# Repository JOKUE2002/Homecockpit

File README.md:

# Homecockpit

## What is it?
The homecockpit is a piece of hardware, that emulates a cockpit for a given computergame.
In this case we're emulating a "universal" cockpit in M$ FSX:SE.
"Universal" means, that it is adapted, so that it can be used on any aircraft type.

## What is the main concept?
The main concept is to have a big frame with cutouts, where panels are _slotted_. 
The frame features:
* space for 7 panels (6x 20x10cm + 1x 10x20cm), 
* a cutout for a monitor to show more complex instruments (PFD, GPS, ...)
* a cutout to fit the saitek yoke
* a powerbar
* an Arduino MEGA as the "brain"

## Which panels are already finished?
* Basic LightsPanel
  * bunch of simple two-state-switches to control lights in and around the aircraft
  * hardware nearly done ( First set of switches done, needs integration with Sim-commands panel)
  * software 0%
* Basic RadioPanel
  * 2 frequency displays + 1 knob (to set s/b freqency)
  * Hardware done (100%)
  * Software still WIP (w/ main firmare)
* AutopilotPanel Part 1
  * CRS, HDG, SPD displays + knobs
  * hardware done (100%)
  * software still WIP (w/ main firmare), but a beta has already been written and tested
* AutopilotPanel Part 2
  * ALT, V/S displays + knobs
  * hardware done (100%)
  * same software as AutopilotPanel Part 1
* Advanced RadioPanel
  * SQUAWK display + setting buttons; com/nav selector/switch buttons
  * hardware work in progress (50% done)
  * software not yet started, but easy (0%)
* Landing gear lever
  * lever with pull function to lock it into three positions (UP, LK, DN)
  * hardware WIP (lever done , installation + wiring missing)
  * software 0%
  
## Which panels are still planned?
* Sim-commands panel
  * buttons to command fsx (pause, slew mode, kneeboard, ...)
* Electrical panel
  * Hydraulics, APU, Generators, ...
* Engine Panel
  * Engine starters, fire suppresion, ...

## What's included?
In the "_pcb_" folder, there are the EAGLE **.sch**ematic/**.b**oa**rd** files for the custom PCBs we designed and ordered to make things easier.
In the "_firmware_" folder there are nearly all iterations of the firmaware, including the current version ("_FSX_3.0_").
In the "_parts_" folder there is a list of all the parts, that have been used to build the cockpit.

## How much is done is it?
If we had to guess this would be like one third done. There are still ~~a few~~ a lot of the planned panels missing. Also the main frame is still a work in progress.

### Individual statuses
* Frame: 70%
* Firmware: 40%
* Panels: 40%
* whole project: 30%

## Who's contributing?
Currently there are two main contributers:
Jonas (Hardware & Software specialist)
Cornelius (Flightsim/flying & design specialist)

## How can you contact us / help us?
Just create an issue. We'll answer on it as soon as possible.

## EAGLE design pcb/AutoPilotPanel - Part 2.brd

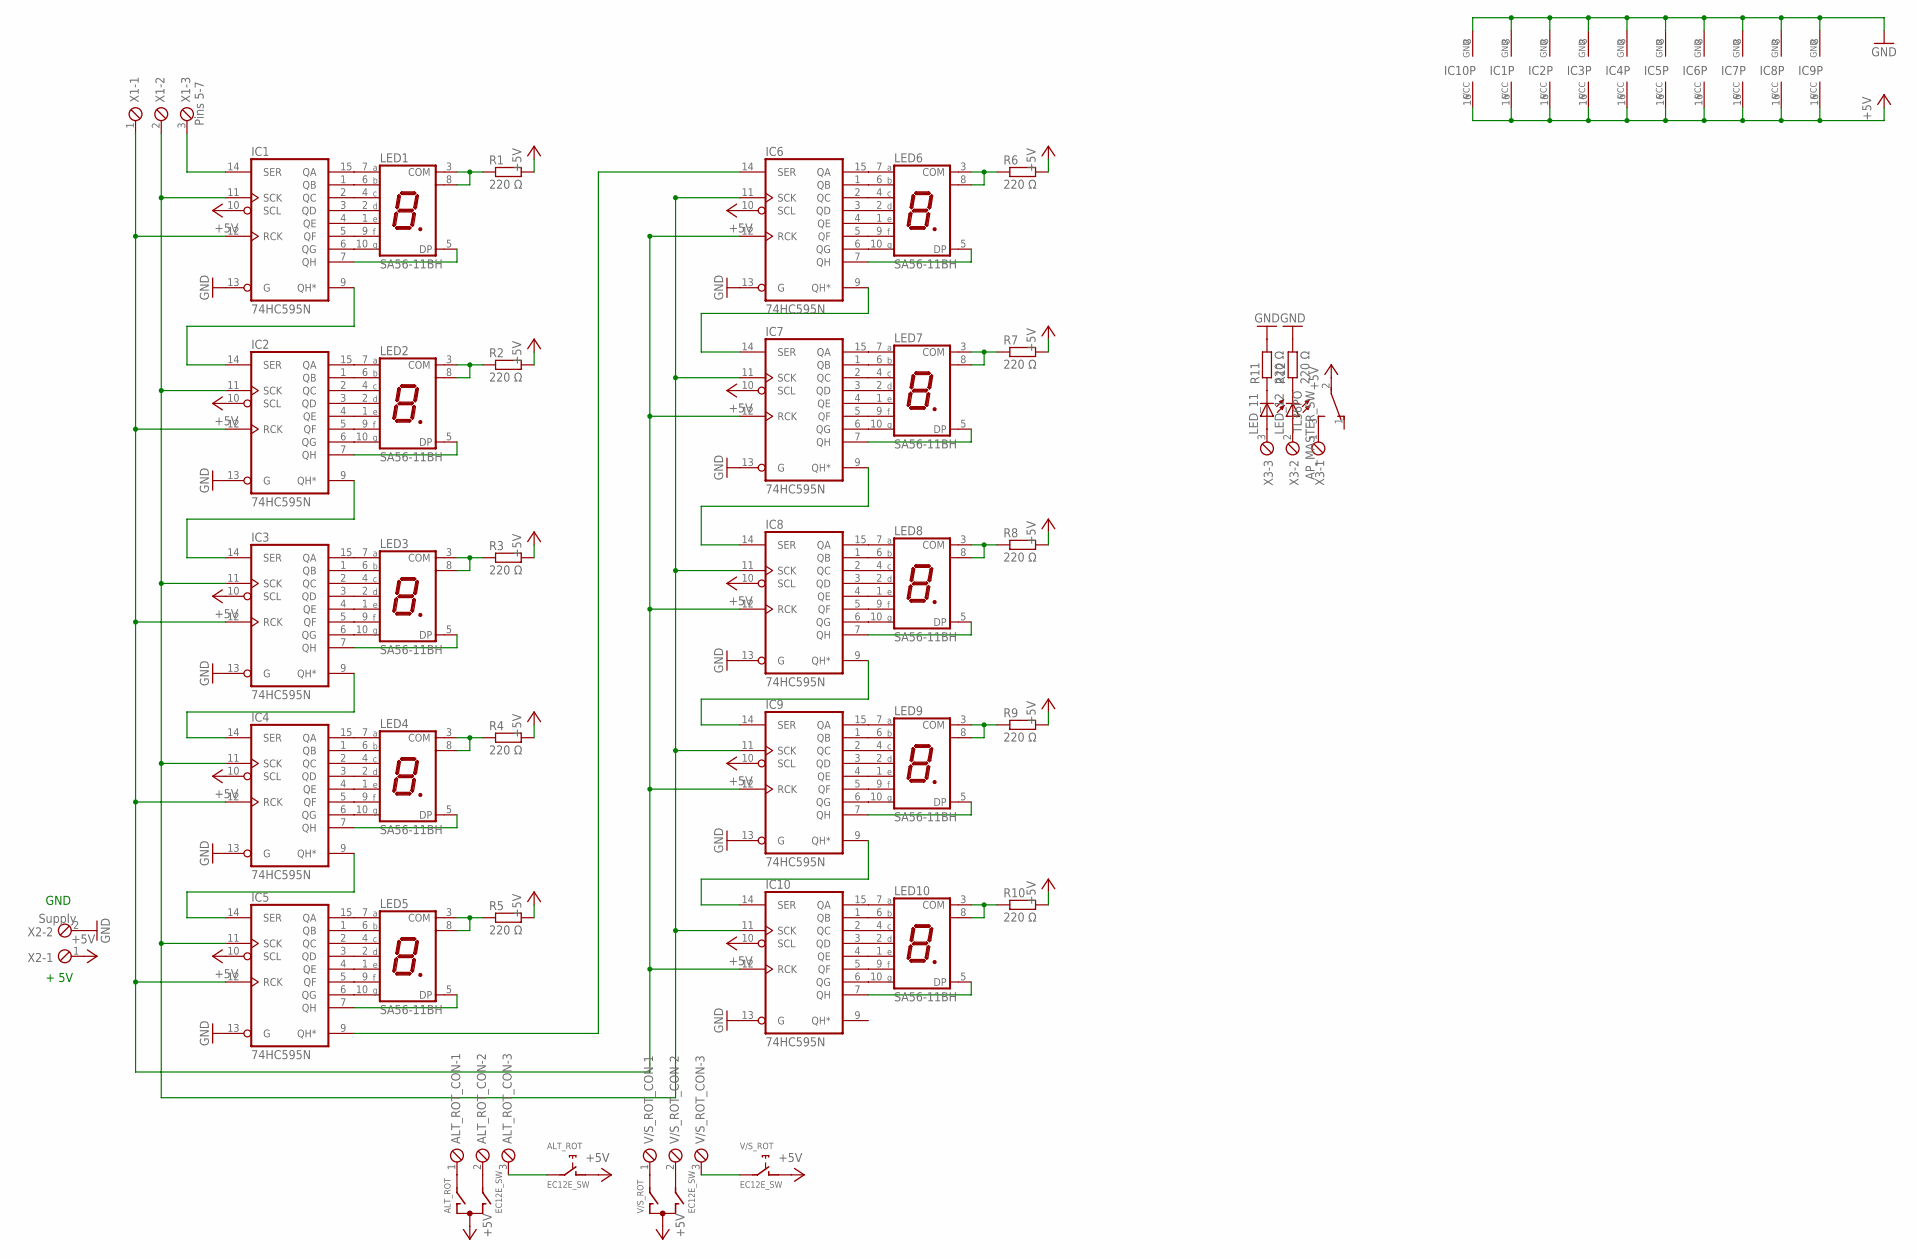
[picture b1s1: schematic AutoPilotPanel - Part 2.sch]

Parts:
ALT_ROT: EC12E_SW; ALPS_EC12E_SW
ALT_ROT_CON: MPT3; 3POL254
AP_MASTER_SW: TL36PO; TL3XPO
IC1, IC2, IC3, IC4, IC5, IC6, IC7, IC8, IC9, IC10: 74HC595N; DIL16
LED1, LED2, LED3, LED4, LED5, LED6, LED7, LED8, LED9, LED10: SA56-11BH; SA56-11
LED_11, LED_12: LED5MM
R1, R2, R3, R4, R5, R6, R7, R8, R9, R10, R11, R12: 220 Ω; 0207/12
V/S_ROT: EC12E_SW; ALPS_EC12E_SW
V/S_ROT_CON: MPT3; 3POL254
X1: Pins 5-7; 3POL254
X2: Supply; 2POL254
X3: MPT3; 3POL254

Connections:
+5V: ALT_ROT.C, ALT_ROT.D (1), AP_MASTER_SW.2, IC1.10 (SCL), IC1.16 (VCC), IC2.10 (SCL), IC2.16 (VCC), IC3.10 (SCL), IC3.16 (VCC), IC4.10 (SCL), IC4.16 (VCC), IC5.10 (SCL), IC5.16 (VCC), IC6.10 (SCL), IC6.16 (VCC), IC7.10 (SCL), IC7.16 (VCC), IC8.10 (SCL), IC8.16 (VCC), IC9.10 (SCL), IC9.16 (VCC), IC10.10 (SCL), IC10.16 (VCC), R1.2, R2.2, R3.2, R4.2, R5.2, R6.2, R7.2, R8.2, R9.2, R10.2, V/S_ROT.C, V/S_ROT.D (1), X2.1
GND: IC1.8 (GND), IC1.13 (G), IC2.8 (GND), IC2.13 (G), IC3.8 (GND), IC3.13 (G), IC4.8 (GND), IC4.13 (G), IC5.8 (GND), IC5.13 (G), IC6.8 (GND), IC6.13 (G), IC7.8 (GND), IC7.13 (G), IC8.8 (GND), IC8.13 (G), IC9.8 (GND), IC9.13 (G), IC10.8 (GND), IC10.13 (G), R11.2, R12.2, X2.2
unnamed: IC1.5 (QF), LED1.9 (F)
unnamed: IC1.3 (QD), LED1.2 (D)
unnamed: IC1.1 (QB), LED1.6 (B)
unnamed: IC1.15 (QA), LED1.7 (A)
unnamed: IC1.2 (QC), LED1.4 (C)
unnamed: IC1.4 (QE), LED1.1 (E)
unnamed: IC1.6 (QG), LED1.10 (G)
unnamed: IC2.5 (QF), LED2.9 (F)
unnamed: IC1.7 (QH), LED1.5 (DP)
unnamed: IC2.3 (QD), LED2.2 (D)
unnamed: IC2.1 (QB), LED2.6 (B)
unnamed: IC1.14 (SER), X1.3
unnamed: IC1.11 (SCK), IC2.11 (SCK), IC3.11 (SCK), IC4.11 (SCK), IC5.11 (SCK), IC6.11 (SCK), IC7.11 (SCK), IC8.11 (SCK), IC9.11 (SCK), IC10.11 (SCK), X1.2
unnamed: IC1.12 (RCK), IC2.12 (RCK), IC3.12 (RCK), IC4.12 (RCK), IC5.12 (RCK), IC6.12 (RCK), IC7.12 (RCK), IC8.12 (RCK), IC9.12 (RCK), IC10.12 (RCK), X1.1
unnamed: LED1.3 (COM), LED1.8 (COM), R1.1
unnamed: IC2.15 (QA), LED2.7 (A)
unnamed: IC2.2 (QC), LED2.4 (C)
unnamed: IC2.4 (QE), LED2.1 (E)
unnamed: IC2.6 (QG), LED2.10 (G)
unnamed: IC3.5 (QF), LED3.9 (F)
unnamed: IC3.3 (QD), LED3.2 (D)
unnamed: IC2.7 (QH), LED2.5 (DP)
unnamed: IC1.9 (QH*), IC2.14 (SER)
unnamed: IC3.1 (QB), LED3.6 (B)
unnamed: IC3.15 (QA), LED3.7 (A)
unnamed: LED2.3 (COM), LED2.8 (COM), R2.1
unnamed: IC3.2 (QC), LED3.4 (C)
unnamed: IC3.4 (QE), LED3.1 (E)
unnamed: IC3.6 (QG), LED3.10 (G)
unnamed: IC4.5 (QF), LED4.9 (F)
unnamed: IC4.3 (QD), LED4.2 (D)
unnamed: IC4.1 (QB), LED4.6 (B)
unnamed: IC4.15 (QA), LED4.7 (A)
unnamed: IC4.2 (QC), LED4.4 (C)
unnamed: IC4.4 (QE), LED4.1 (E)
unnamed: IC4.6 (QG), LED4.10 (G)
unnamed: IC5.5 (QF), LED5.9 (F)
unnamed: IC5.3 (QD), LED5.2 (D)
unnamed: IC5.1 (QB), LED5.6 (B)
unnamed: IC5.15 (QA), LED5.7 (A)
unnamed: IC5.2 (QC), LED5.4 (C)
unnamed: IC3.7 (QH), LED3.5 (DP)
unnamed: IC2.9 (QH*), IC3.14 (SER)
unnamed: IC5.4 (QE), LED5.1 (E)
unnamed: IC5.6 (QG), LED5.10 (G)
unnamed: LED3.3 (COM), LED3.8 (COM), R3.1
unnamed: IC6.5 (QF), LED6.9 (F)
unnamed: IC6.3 (QD), LED6.2 (D)
unnamed: IC6.1 (QB), LED6.6 (B)
unnamed: IC6.15 (QA), LED6.7 (A)
unnamed: IC6.2 (QC), LED6.4 (C)
unnamed: IC6.4 (QE), LED6.1 (E)
unnamed: IC6.6 (QG), LED6.10 (G)
unnamed: IC7.5 (QF), LED7.9 (F)
unnamed: IC7.3 (QD), LED7.2 (D)
unnamed: IC7.1 (QB), LED7.6 (B)
unnamed: IC7.15 (QA), LED7.7 (A)
unnamed: IC7.2 (QC), LED7.4 (C)
unnamed: IC7.4 (QE), LED7.1 (E)
unnamed: IC7.6 (QG), LED7.10 (G)
unnamed: IC8.5 (QF), LED8.9 (F)
unnamed: IC4.7 (QH), LED4.5 (DP)
unnamed: IC3.9 (QH*), IC4.14 (SER)
unnamed: IC8.3 (QD), LED8.2 (D)
unnamed: IC8.1 (QB), LED8.6 (B)
unnamed: LED4.3 (COM), LED4.8 (COM), R4.1
unnamed: IC8.15 (QA), LED8.7 (A)
unnamed: IC8.2 (QC), LED8.4 (C)
unnamed: IC8.4 (QE), LED8.1 (E)
unnamed: IC8.6 (QG), LED8.10 (G)
unnamed: IC9.5 (QF), LED9.9 (F)
unnamed: IC9.3 (QD), LED9.2 (D)
unnamed: IC9.1 (QB), LED9.6 (B)
unnamed: IC9.15 (QA), LED9.7 (A)
unnamed: IC9.2 (QC), LED9.4 (C)
unnamed: IC9.4 (QE), LED9.1 (E)
unnamed: IC9.6 (QG), LED9.10 (G)
unnamed: AP_MASTER_SW.3 (S), X3.1
unnamed: LED_12.A, X3.2
unnamed: LED_11.A, X3.3
unnamed: LED_11.K (C), R11.1
unnamed: IC5.7 (QH), LED5.5 (DP)
unnamed: IC4.9 (QH*), IC5.14 (SER)
unnamed: LED_12.K (C), R12.1
unnamed: LED5.3 (COM), LED5.8 (COM), R5.1
unnamed: ALT_ROT.A, ALT_ROT_CON.1
unnamed: ALT_ROT.B, ALT_ROT_CON.2
unnamed: ALT_ROT.E (2), ALT_ROT_CON.3
unnamed: IC10.7 (QH), LED10.5 (DP)
unnamed: IC9.9 (QH*), IC10.14 (SER)
unnamed: LED10.3 (COM), LED10.8 (COM), R10.1
unnamed: IC10.5 (QF), LED10.9 (F)
unnamed: IC10.3 (QD), LED10.2 (D)
unnamed: IC10.1 (QB), LED10.6 (B)
unnamed: IC10.15 (QA), LED10.7 (A)
unnamed: IC10.2 (QC), LED10.4 (C)
unnamed: IC10.4 (QE), LED10.1 (E)
unnamed: IC6.7 (QH), LED6.5 (DP)
unnamed: IC5.9 (QH*), IC6.14 (SER)
unnamed: IC10.6 (QG), LED10.10 (G)
unnamed: LED6.3 (COM), LED6.8 (COM), R6.1
unnamed: V/S_ROT.A, V/S_ROT_CON.1
unnamed: V/S_ROT.B, V/S_ROT_CON.2
unnamed: IC7.7 (QH), LED7.5 (DP)
unnamed: IC6.9 (QH*), IC7.14 (SER)
unnamed: LED7.3 (COM), LED7.8 (COM), R7.1
unnamed: IC8.7 (QH), LED8.5 (DP)
unnamed: IC7.9 (QH*), IC8.14 (SER)
unnamed: LED8.3 (COM), LED8.8 (COM), R8.1
unnamed: IC9.7 (QH), LED9.5 (DP)
unnamed: IC8.9 (QH*), IC9.14 (SER)
unnamed: LED9.3 (COM), LED9.8 (COM), R9.1
unnamed: V/S_ROT.E (2), V/S_ROT_CON.3

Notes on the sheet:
+ 5V
GND

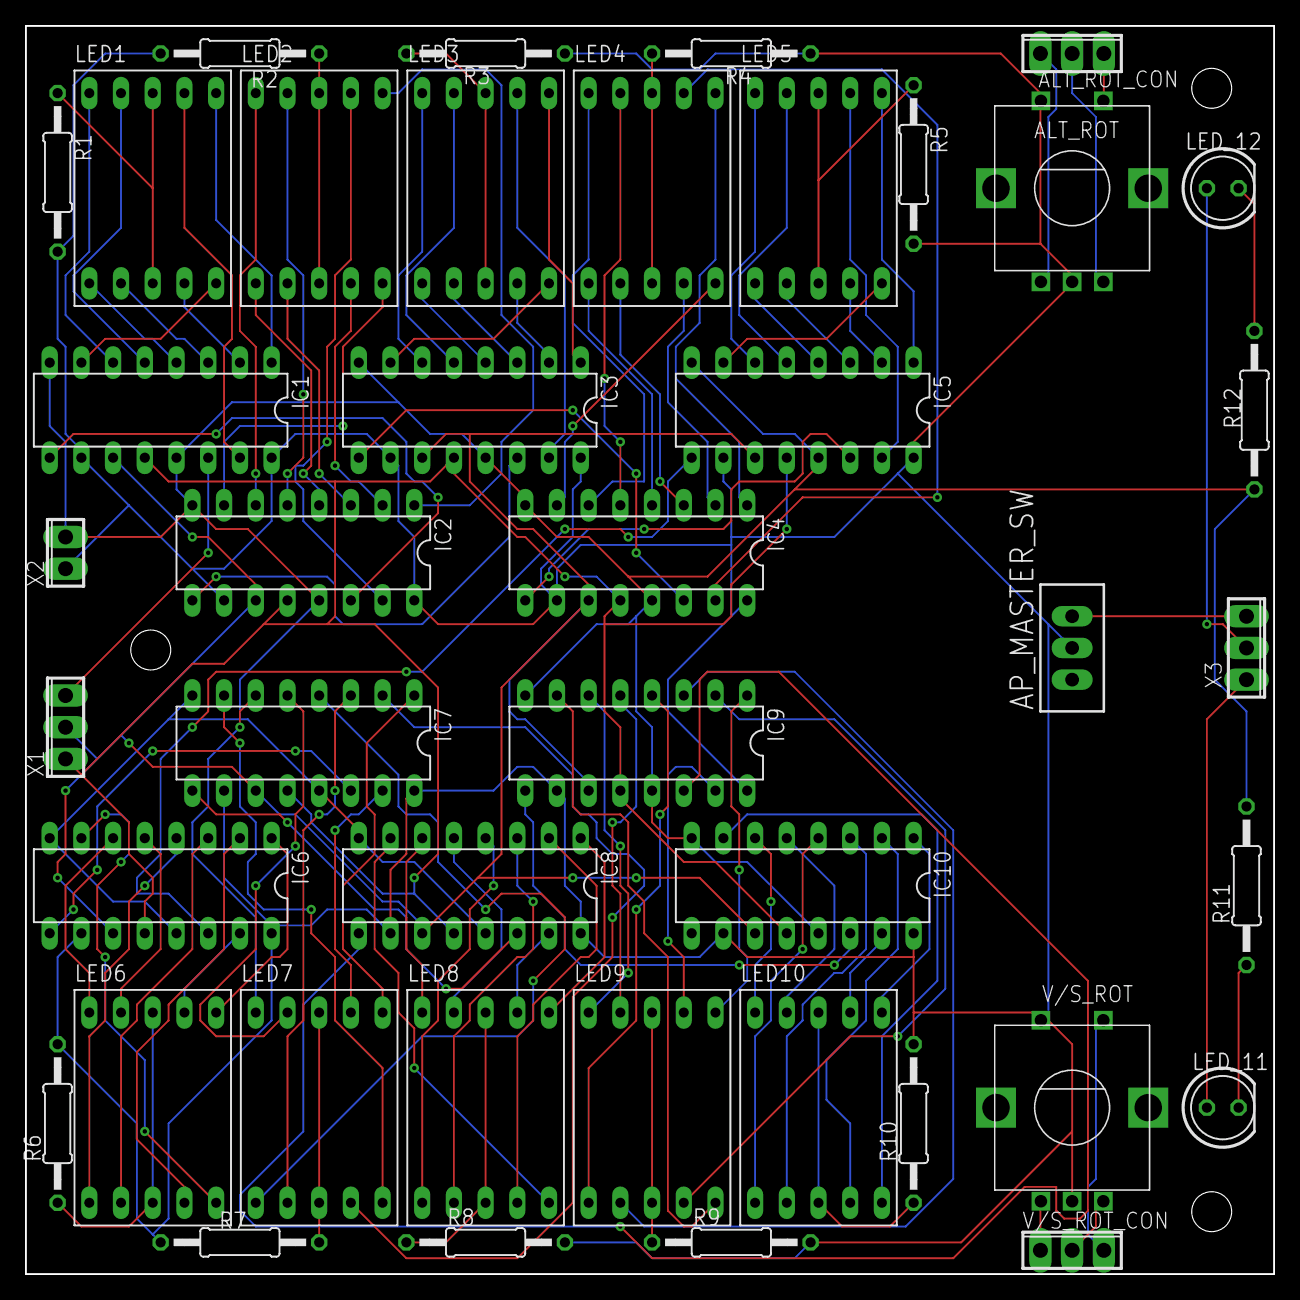
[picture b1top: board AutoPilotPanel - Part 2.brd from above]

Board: 2 copper layers, 100.0 x 100.0 mm, 42 parts (0 on the bottom side), 115 nets.

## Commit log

2019-07-09 Data upload
    Uploading a whole bunch of data from my pc
2019-07-09 Renamed files
    Files renamed + packaged the way arduino likes it
2019-07-11 added pinmapping and extraction images
2019-07-11 fixed a typo
2019-07-15 Added Radios to firmware
    Firmware v3.1 w/ Com1, Com2, Nav1, Nav2 (active+sb)
2019-07-17 Update 17/07/19
    Corrected spelling mistakes, as well as updating the panel planning/ panel working section
2019-07-17 Update C section
2020-07-22 Firmware v4
    In this update we changed the firmware design by adding delays to the displaysroutines spliting parts of the displaying (only the display with the changed bits gets an update). This also addresses th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
    Note: Only the AP1 module has been implemented (yet), due to unfinished designchoises regarding the decimal point in the com/nav modules.
    It also hasn't been tested (yet), but I'm up to it.
